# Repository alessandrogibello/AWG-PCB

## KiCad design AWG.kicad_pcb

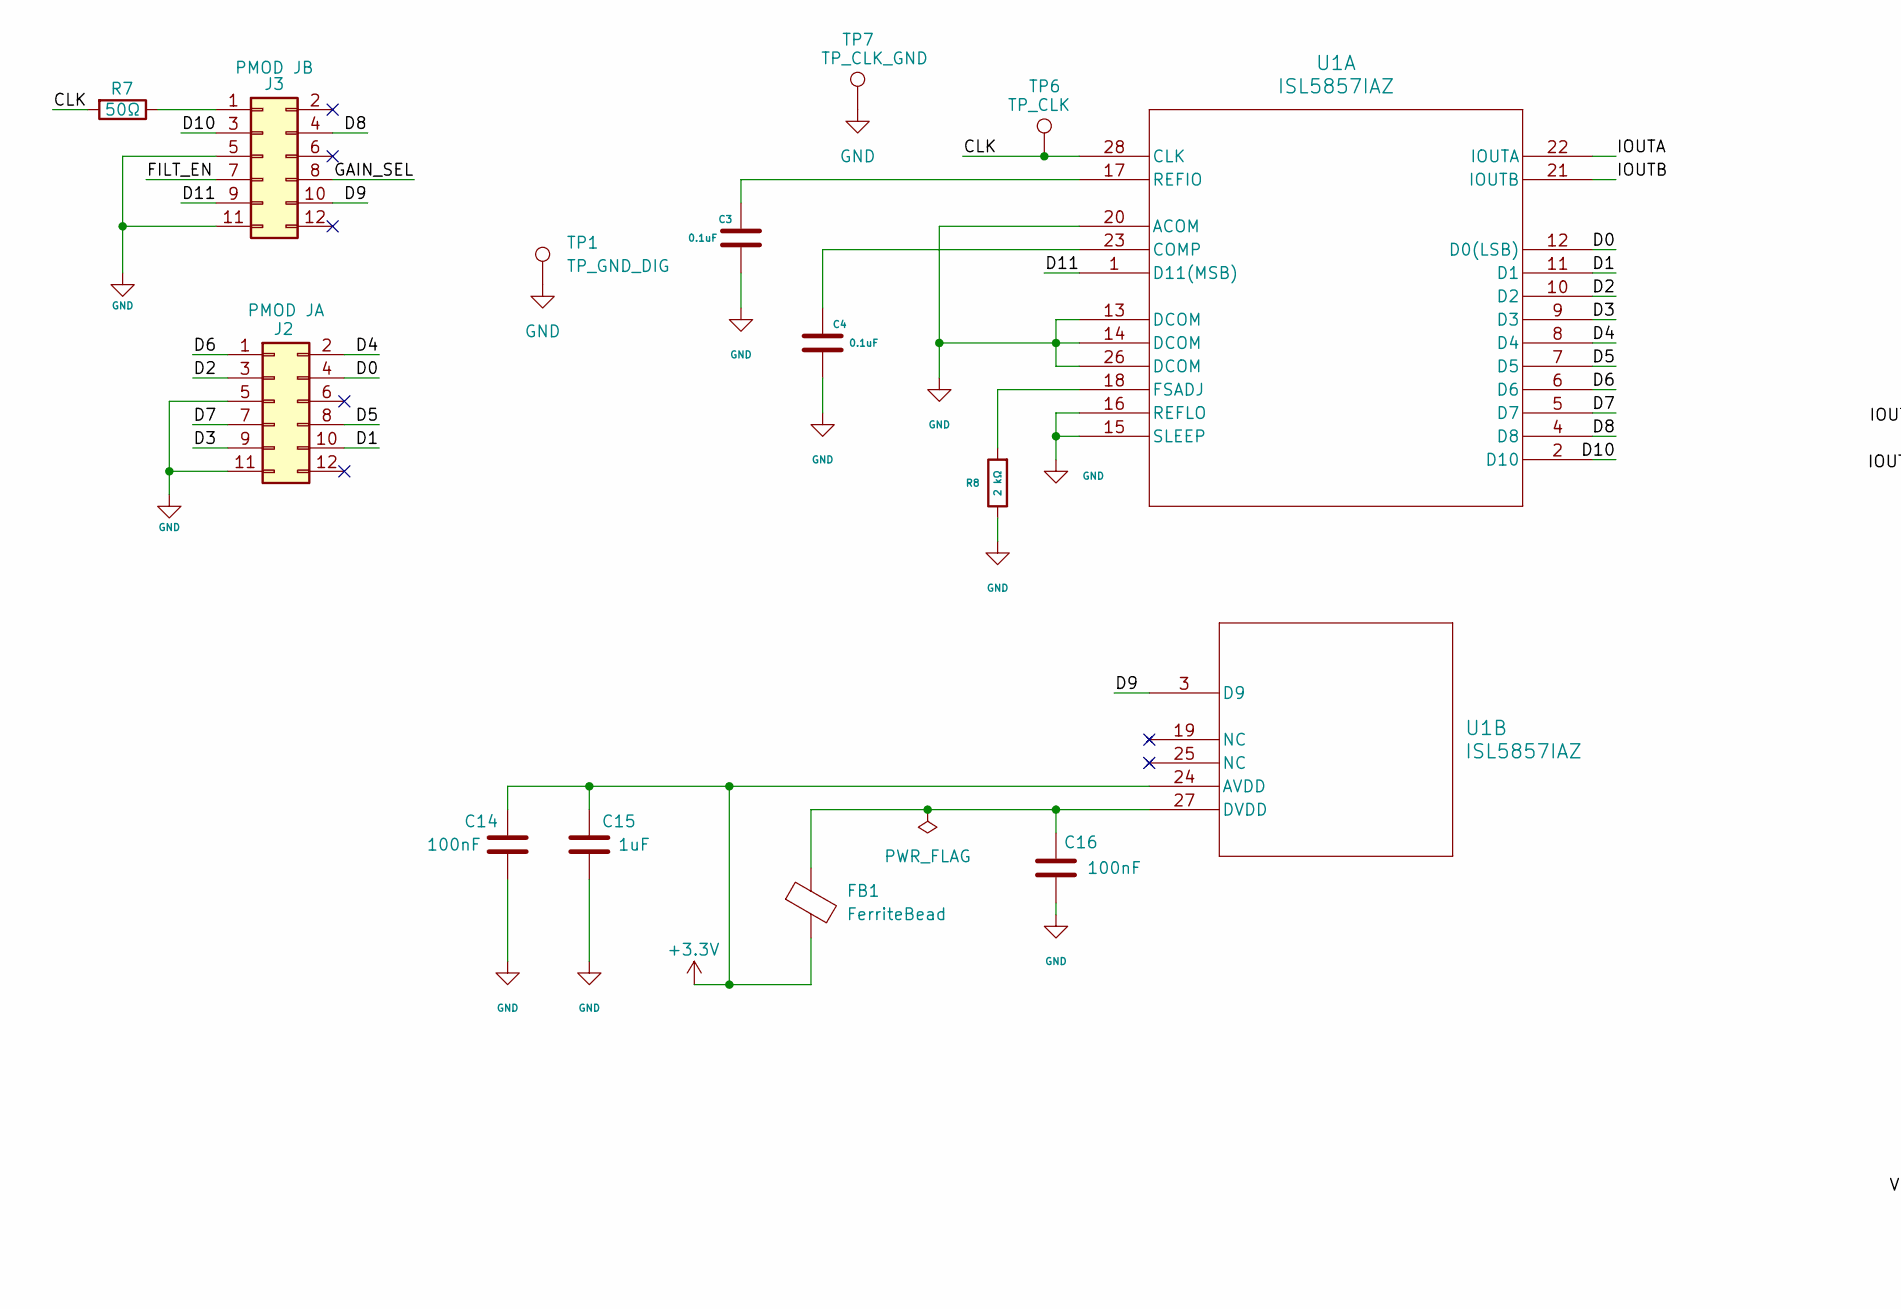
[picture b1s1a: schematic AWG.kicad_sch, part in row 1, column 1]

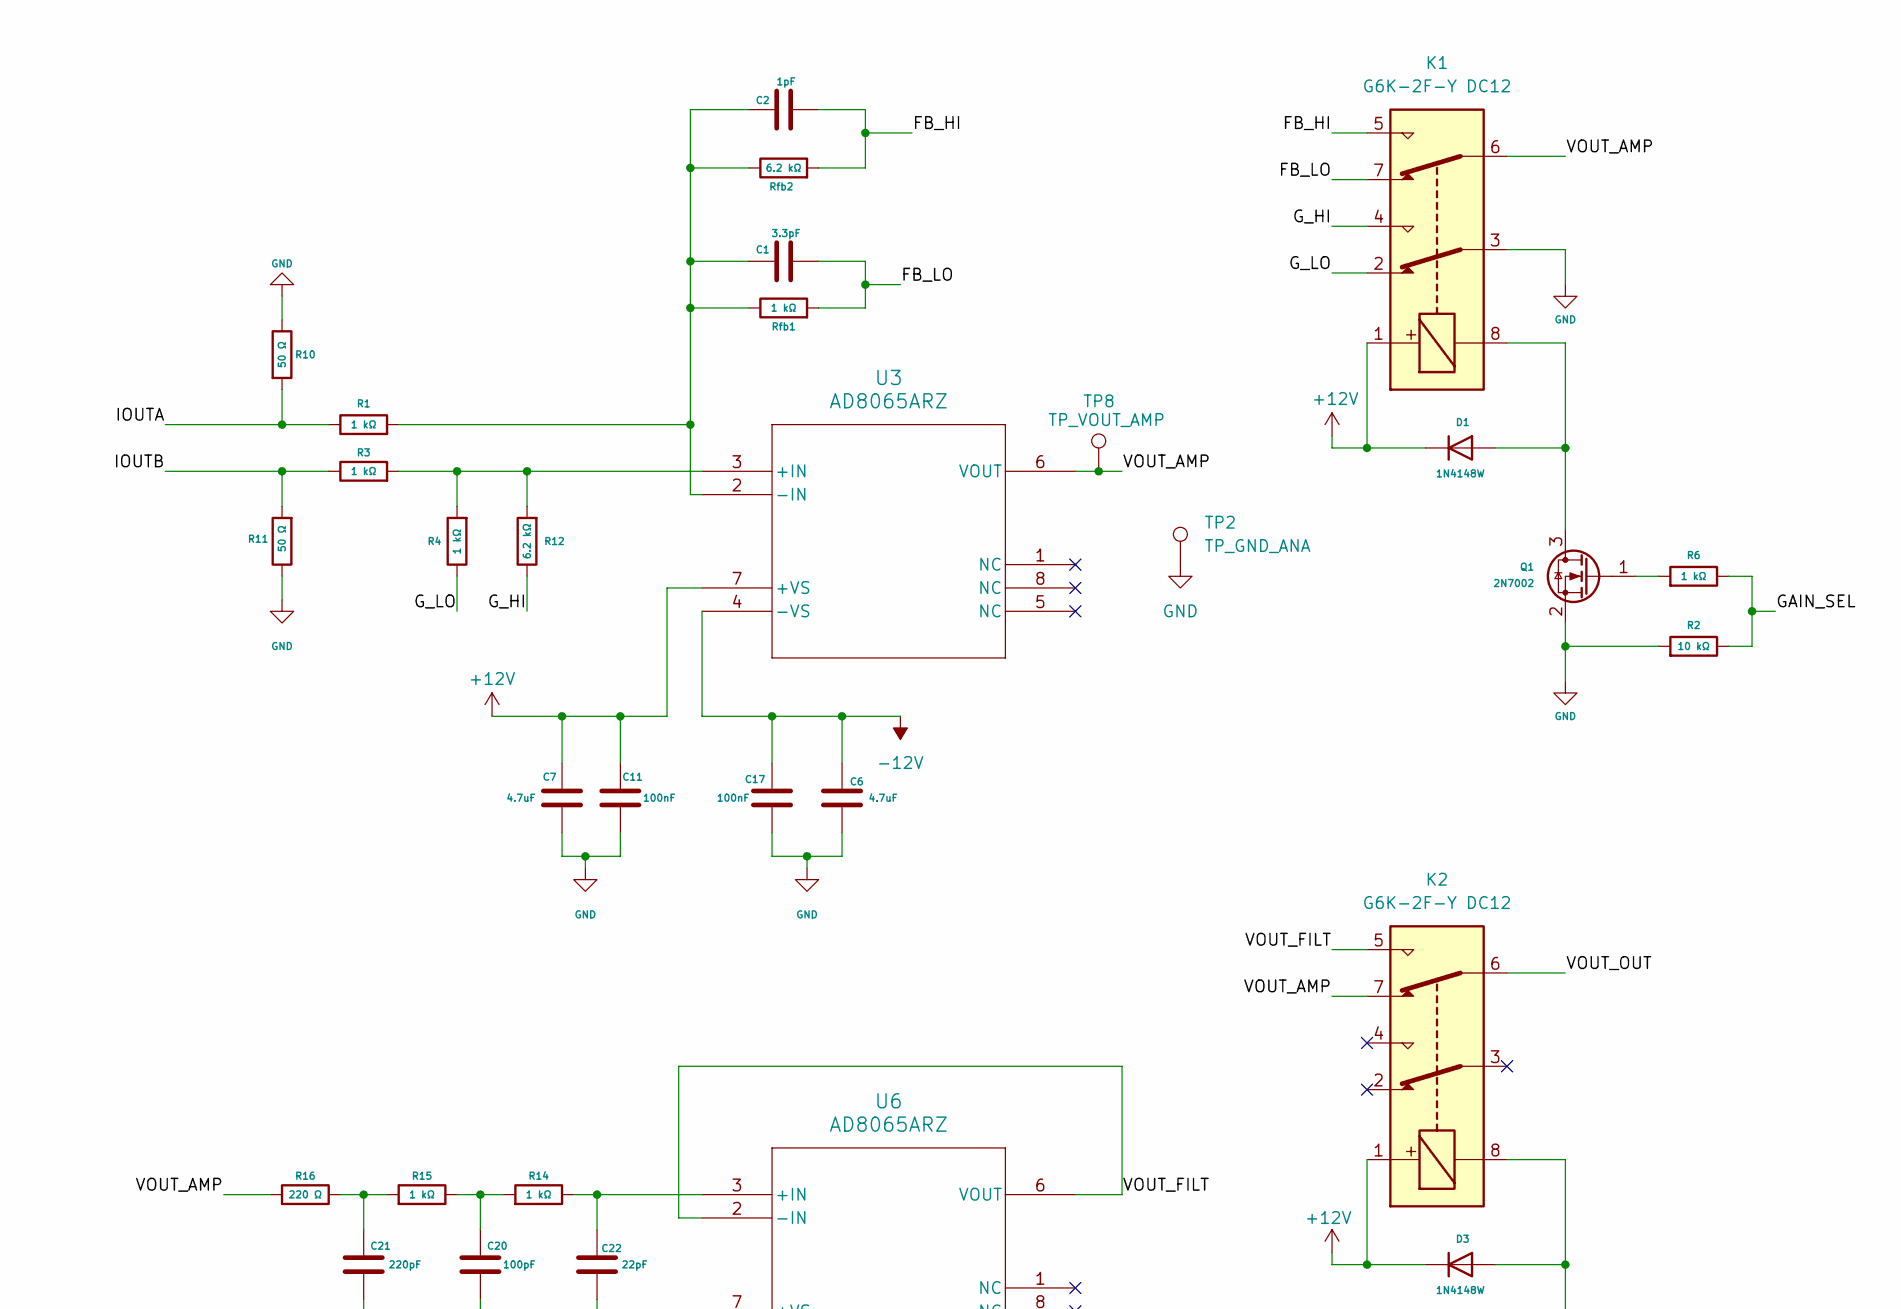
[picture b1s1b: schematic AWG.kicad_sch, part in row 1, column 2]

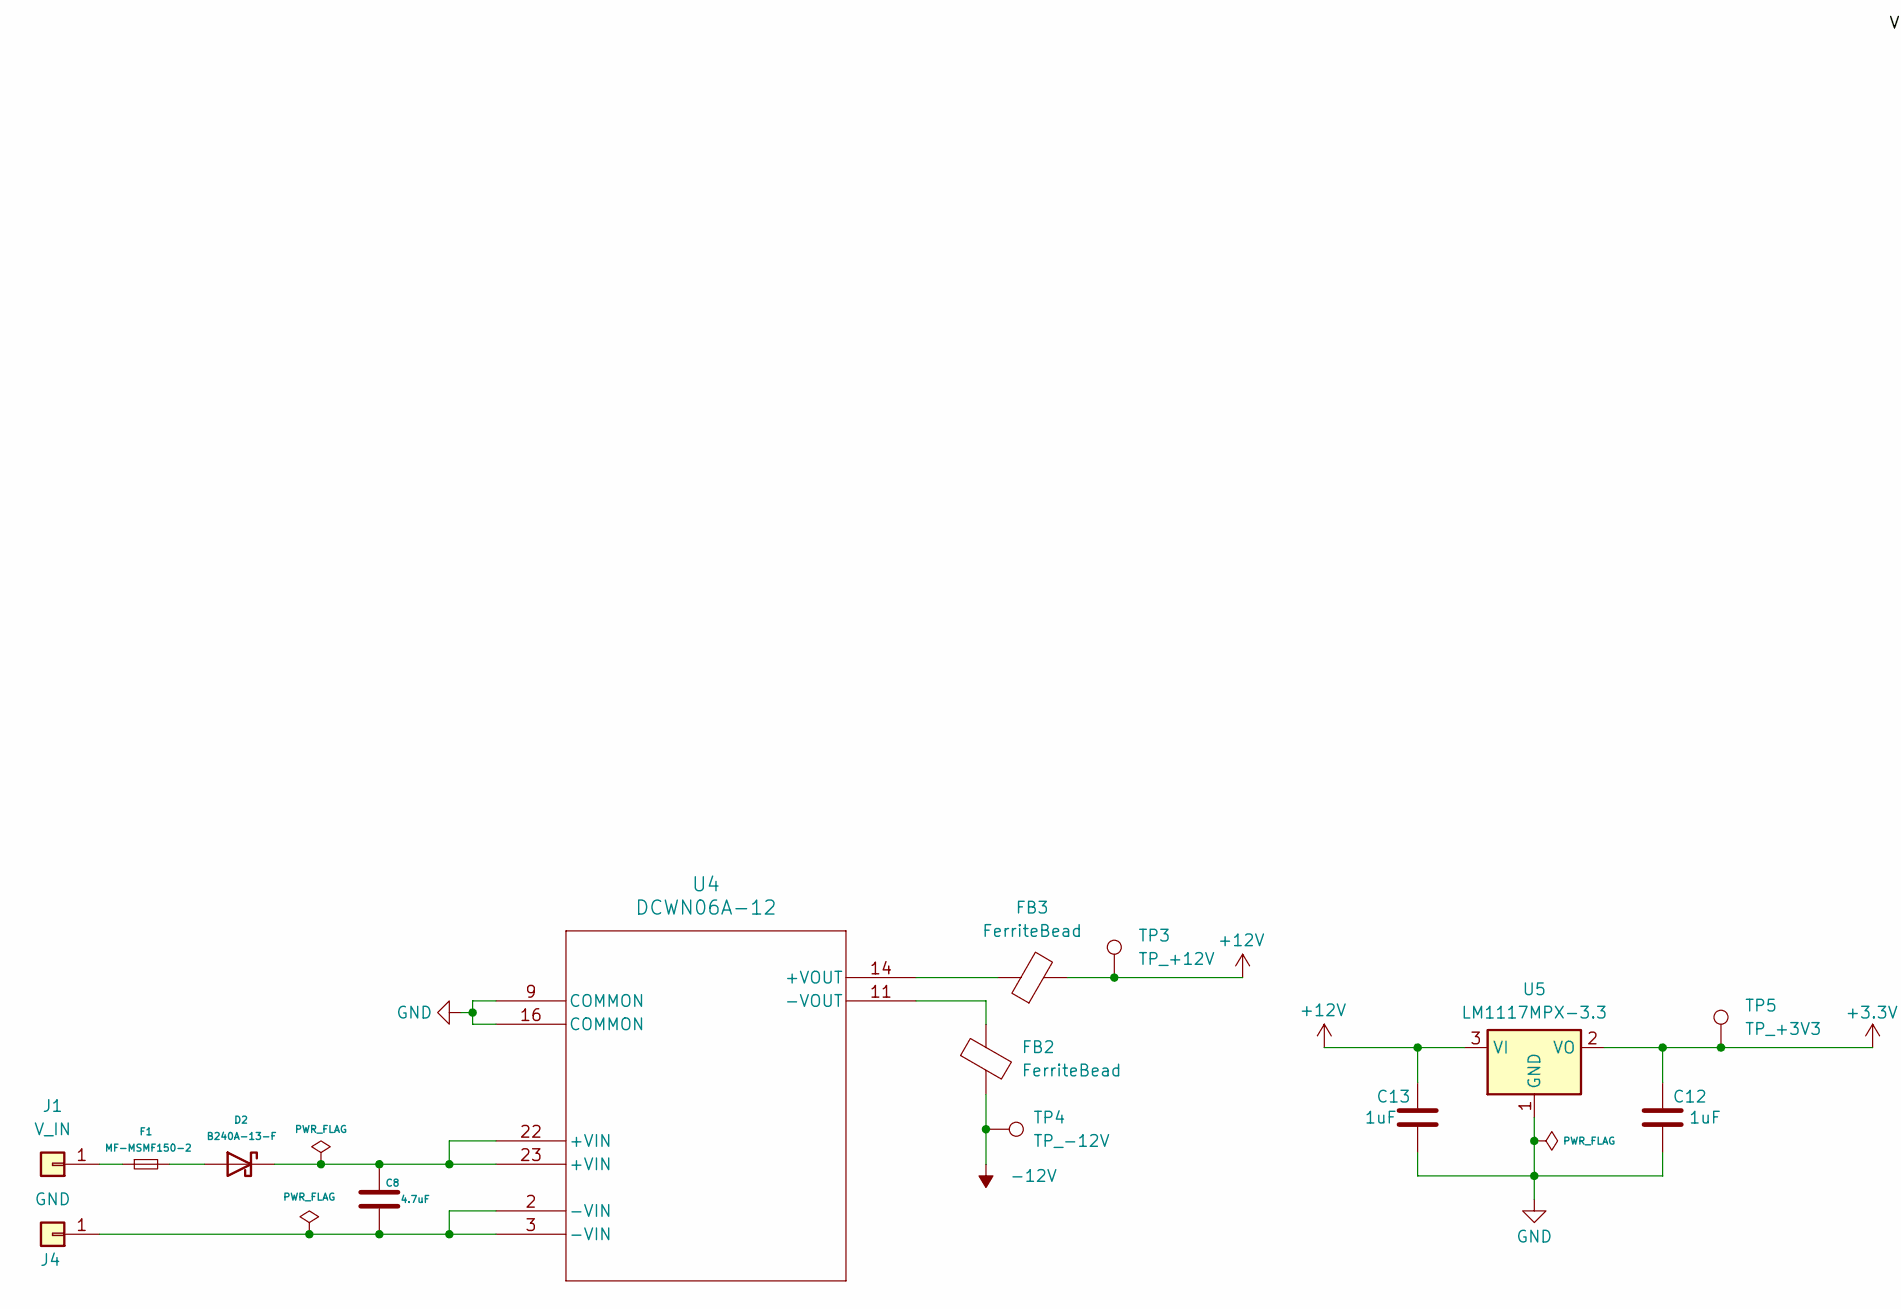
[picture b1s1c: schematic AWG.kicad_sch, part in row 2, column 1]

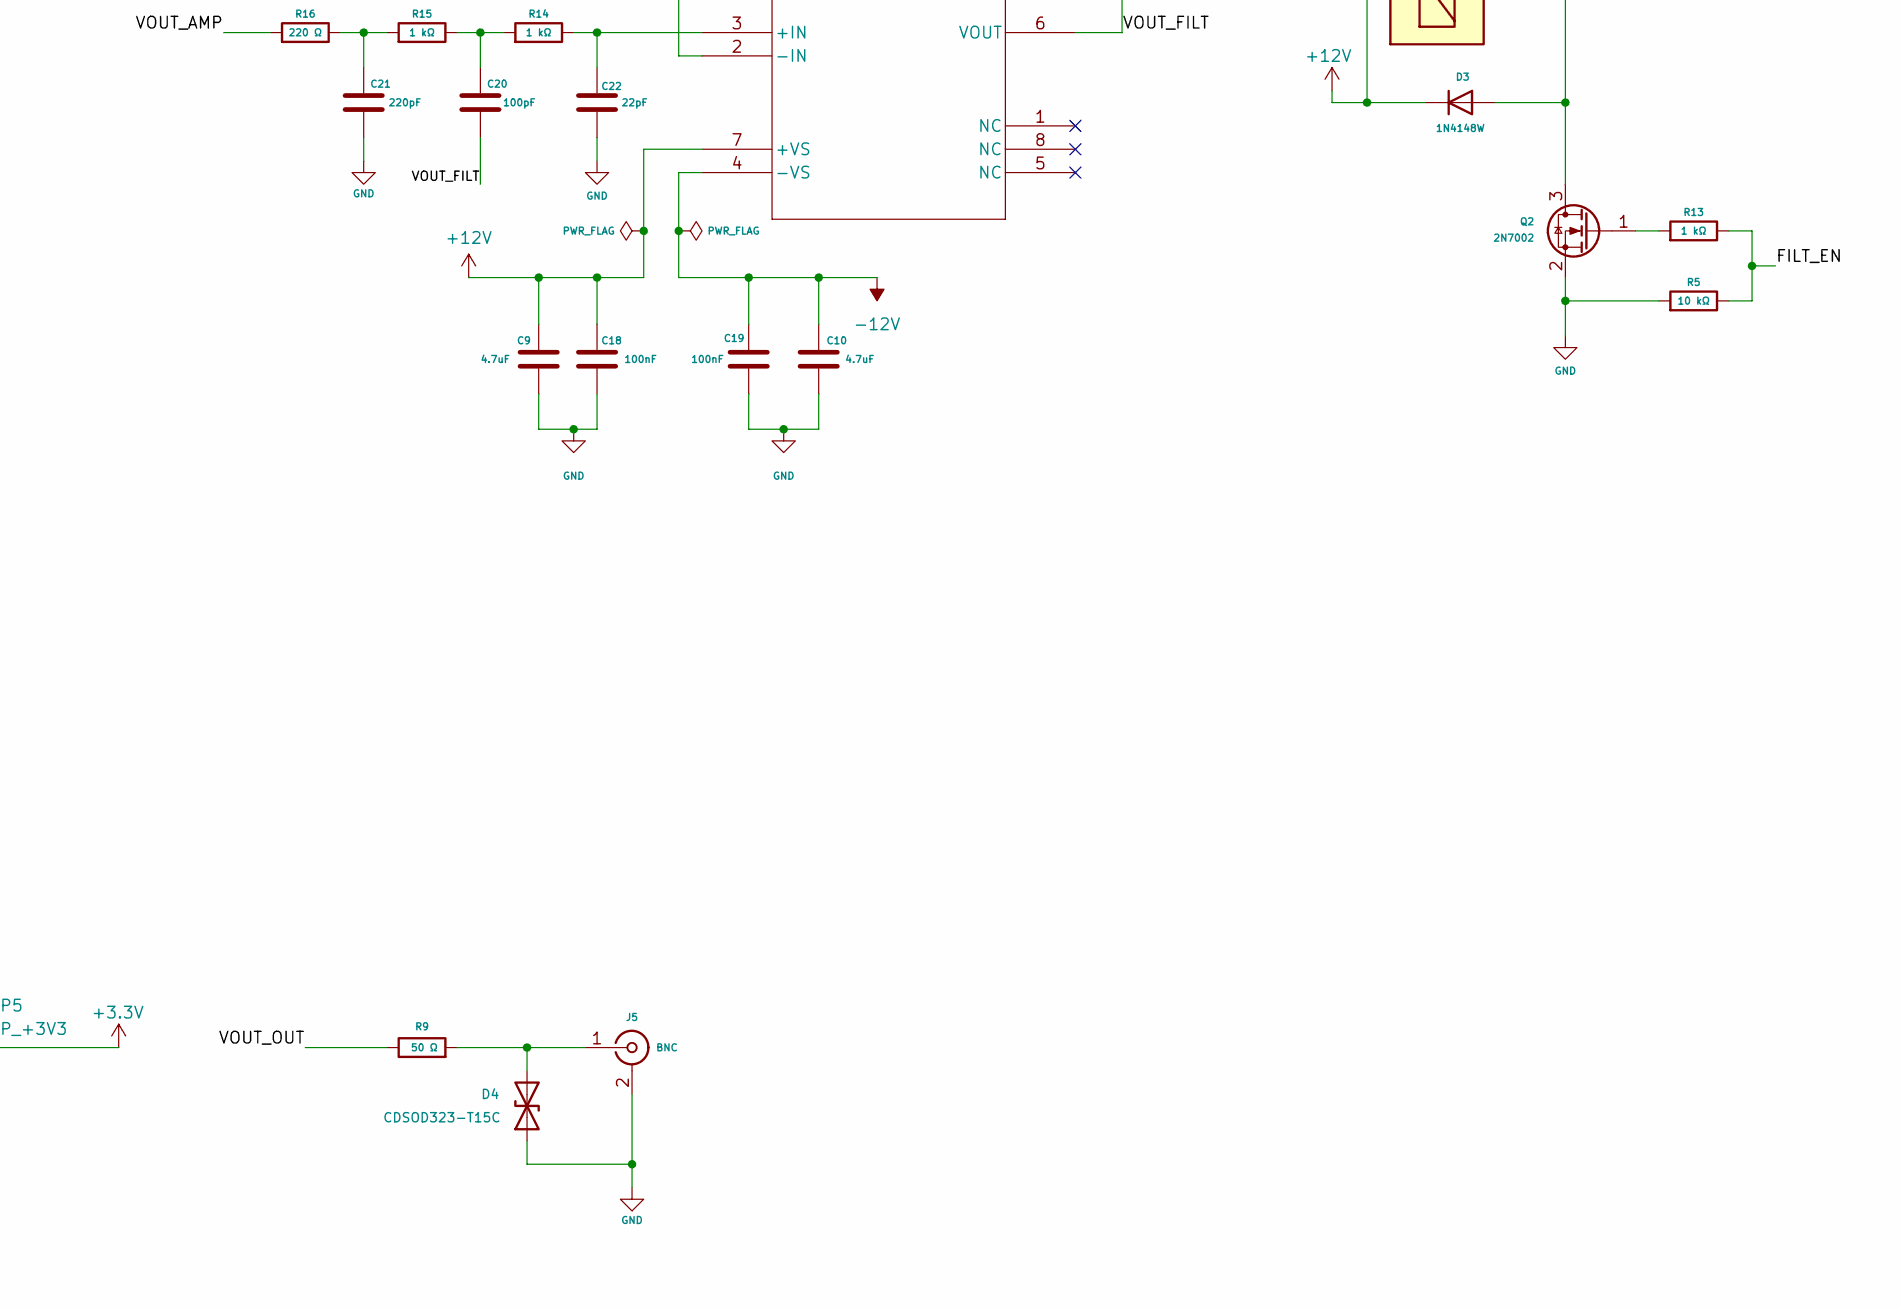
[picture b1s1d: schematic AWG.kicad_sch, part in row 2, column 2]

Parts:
C1: 3.3pF; C_0805_2012Metric_Pad1.18x1.45mm_HandSolder
C2: 1pF; C_0805_2012Metric_Pad1.18x1.45mm_HandSolder
C3, C4: 0.1uF; C_0805_2012Metric_Pad1.18x1.45mm_HandSolder
C6, C7, C8, C9, C10: 4.7uF; C_0805_2012Metric_Pad1.18x1.45mm_HandSolder
C11, C14, C16, C17, C18, C19: 100nF; C_0805_2012Metric_Pad1.18x1.45mm_HandSolder
C12, C13, C15: 1uF; C_0805_2012Metric_Pad1.18x1.45mm_HandSolder
C20: 100pF; C_0805_2012Metric_Pad1.18x1.45mm_HandSolder
C21: 220pF; C_0805_2012Metric_Pad1.18x1.45mm_HandSolder
C22: 22pF; C_0805_2012Metric_Pad1.18x1.45mm_HandSolder
D1, D3: 1N4148W; D_SOD-123
D2: B240A-13-F; D_SMA
D4: CDSOD323-T15C; D_SOD-323_HandSoldering
F1: MF-MSMF150-2; Fuse_1812_4532Metric_Pad1.30x3.40mm_HandSolder
FB1, FB2, FB3: FerriteBead; L_0603_1608Metric
J1: V_IN; Banana_Jack_1Pin
J2: PMOD JA; PinHeader_2x06_P2.54mm_Horizontal
J3: PMOD JB; PinHeader_2x06_P2.54mm_Horizontal
J4: GND; Banana_Jack_1Pin
J5: BNC; BNC_Amphenol_B6252HB-NPP3G-50_Horizontal
K1, K2: G6K-2F-Y DC12; Relay_DPDT_Omron_G6K-2F-Y
Q1, Q2: 2N7002; SOT-23
R1, R3, R4, R6, R13, R14, R15: 1 kΩ; R_0805_2012Metric_Pad1.20x1.40mm_HandSolder
R2, R5: 10 kΩ; R_0805_2012Metric_Pad1.20x1.40mm_HandSolder
R7: 50Ω; R_0805_2012Metric_Pad1.20x1.40mm_HandSolder
R8: 2 kΩ; R_0805_2012Metric_Pad1.20x1.40mm_HandSolder
R9, R10, R11: 50 Ω; R_0805_2012Metric_Pad1.20x1.40mm_HandSolder
R12: 6.2 kΩ; R_0805_2012Metric_Pad1.20x1.40mm_HandSolder
R16: 220 Ω; R_0805_2012Metric_Pad1.20x1.40mm_HandSolder
Rfb1: 1 kΩ; R_0805_2012Metric_Pad1.20x1.40mm_HandSolder
Rfb2: 6.2 kΩ; R_0805_2012Metric_Pad1.20x1.40mm_HandSolder
TP1: TP_GND_DIG; TestPoint_Loop_D2.50mm_Drill1.0mm
TP2: TP_GND_ANA; TestPoint_Pad_D1.0mm
TP3: TP_+12V; TestPoint_Pad_D1.5mm
TP4: TP_-12V; TestPoint_Pad_D1.5mm
TP5: TP_+3V3; TestPoint_Pad_D1.5mm
TP6: TP_CLK; TestPoint_Pad_D1.0mm
TP7: TP_CLK_GND; TestPoint_Pad_D1.0mm
TP8: TP_VOUT_AMP; TestPoint_Pad_D1.0mm
U1: ISL5857IAZ; TSSOP28_4P50X9P80_INR-M
U3, U6: AD8065ARZ; R_8_ADI
U4: DCWN06A-12; 3W_DIP_MWU
U5: LM1117MPX-3.3; SOT-223-3_TabPin2

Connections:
+3.3V: C12.1, C14.1, C15.1, FB1.2, TP5.1 (1_1), U1.24 (AVDD), U5.2 (VO)
+12V: C7.1, C9.1, C11.1, C13.1, C18.1, D1.1 (K), D3.1 (K), FB3.2, K1.1, K2.1, TP3.1 (1_1), U3.7 (+VS), U5.3 (VI), U6.7 (+VS)
-12V: C6.1, C10.1, C17.1, C19.1, FB2.2, TP4.1 (1_1), U3.4 (-VS), U6.4 (-VS)
/CLK: R7.2, TP6.1 (1_1), U1.28 (CLK)
/D0: J2.4, U1.12 (D0(LSB))
/D1: J2.10, U1.11 (D1)
/D2: J2.3, U1.10 (D2)
/D3: J2.9, U1.9 (D3)
/D4: J2.2, U1.8 (D4)
/D5: J2.8, U1.7 (D5)
/D6: J2.1, U1.6 (D6)
/D7: J2.7, U1.5 (D7)
/D8: J3.4, U1.4 (D8)
/D9: J3.10, U1.3 (D9)
/D10: J3.3, U1.2 (D10)
/D11: J3.9, U1.1 (D11(MSB))
/FB_HI: C2.2, K1.5, Rfb2.2
/FB_LO: C1.2, K1.7, Rfb1.2
/FILT_EN: J3.7, R5.1, R13.1
/GAIN_SEL: J3.8, R2.1, R6.1
/G_HI: K1.4, R12.1
/G_LO: K1.2, R4.1
/IOUTA: R1.1, R10.2, U1.22 (IOUTA)
/IOUTB: R3.1, R11.2, U1.21 (IOUTB)
/VOUT_AMP: K1.6, K2.7, R16.2, TP8.1 (1_1), U3.6 (VOUT)
/VOUT_FILT: C20.2, K2.5, U6.2 (-IN), U6.6 (VOUT)
/VOUT_OUT: K2.6, R9.1
GND: C3.2, C4.2, C6.2, C7.2, C9.2, C10.2, C11.2, C12.2, C13.2, C14.2, C15.2, C16.2, C17.2, C18.2, C19.2, C21.2, C22.2, D4.1 (A1), J2.5, J2.11, J3.5, J3.11, J5.2 (Ext), K1.3, Q1.2 (S), Q2.2 (S), R2.2, R5.2, R8.1, R10.1, R11.1, TP1.1 (1_1), TP2.1 (1_1), TP7.1 (1_1), U1.13 (DCOM), U1.14 (DCOM), U1.15 (SLEEP), U1.16 (REFLO), U1.20 (ACOM), U1.26 (DCOM), U4.9 (COMMON), U4.16 (COMMON), U5.1 (GND)
unnamed: C20.1, R14.2, R15.1
unnamed: C21.1, R15.2, R16.1
unnamed: D1.2 (A), K1.8, Q1.3 (D)
unnamed: D2.2 (A), F1.2
unnamed: C8.1, D2.1 (K), U4.22 (+VIN), U4.23 (+VIN)
unnamed: D3.2 (A), K2.8, Q2.3 (D)
unnamed: D4.2 (A2), J5.1 (In), R9.2
unnamed: F1.1, J1.1 (Pin_1_1)
unnamed: J3.1, R7.1
unnamed: C8.2, J4.1 (Pin_1_1), U4.2 (-VIN), U4.3 (-VIN)
unnamed: Q1.1 (G), R6.2
unnamed: Q2.1 (G), R13.2
unnamed: C4.1, U1.23 (COMP)
unnamed: R8.2, U1.18 (FSADJ)
unnamed: C3.1, U1.17 (REFIO)
unnamed: C16.1, FB1.1, U1.27 (DVDD)
unnamed: R3.2, R4.2, R12.2, U3.3 (+IN)
unnamed: C1.1, C2.1, R1.2, Rfb1.1, Rfb2.1, U3.2 (-IN)
unnamed: FB3.1, U4.14 (+VOUT)
unnamed: FB2.1, U4.11 (-VOUT)
unnamed: C22.1, R14.1, U6.3 (+IN)

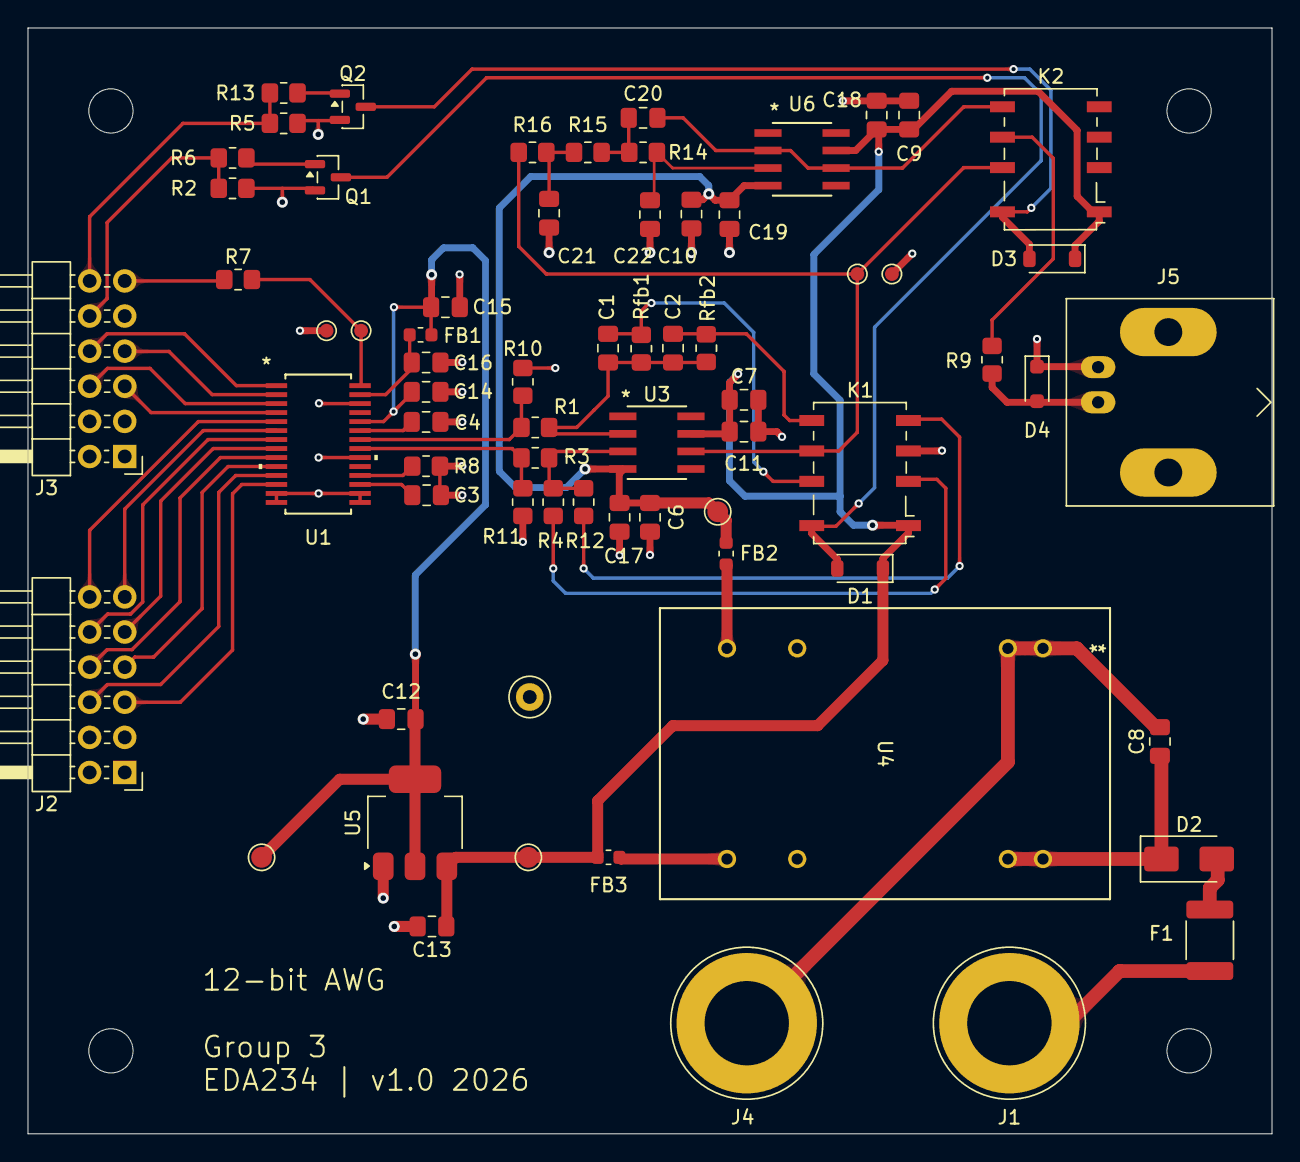
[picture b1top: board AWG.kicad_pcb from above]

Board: 2 copper layers, 90.0 x 80.0 mm, 69 parts (0 on the bottom side), 49 nets.
